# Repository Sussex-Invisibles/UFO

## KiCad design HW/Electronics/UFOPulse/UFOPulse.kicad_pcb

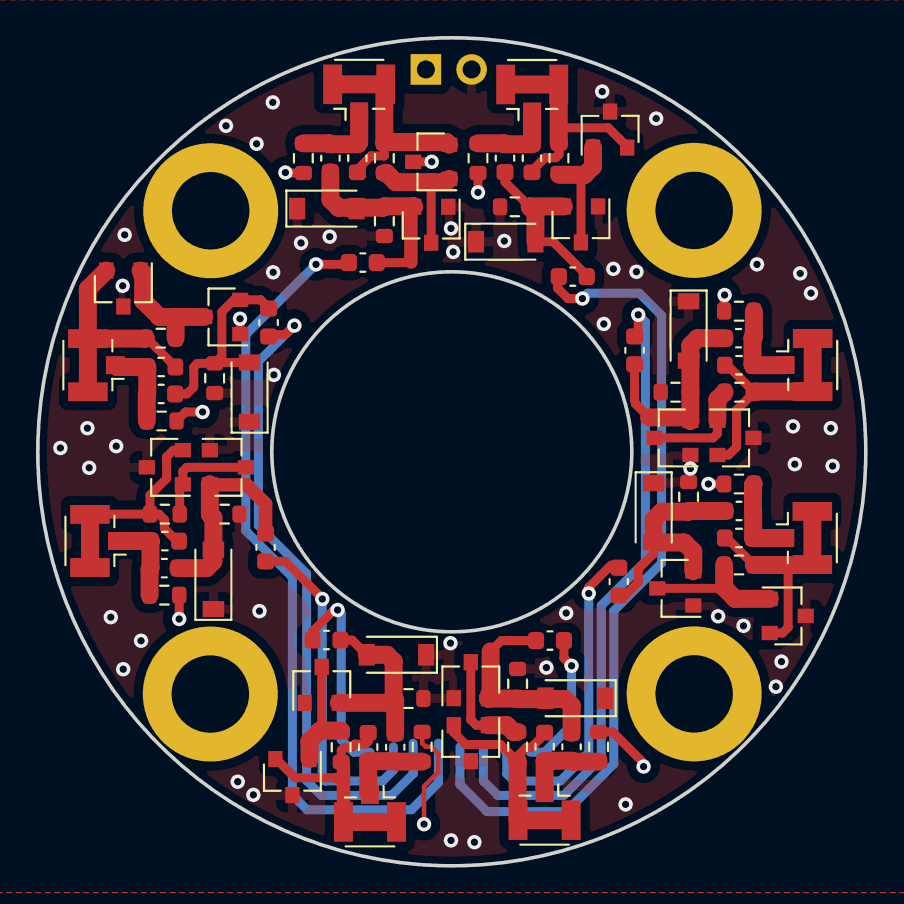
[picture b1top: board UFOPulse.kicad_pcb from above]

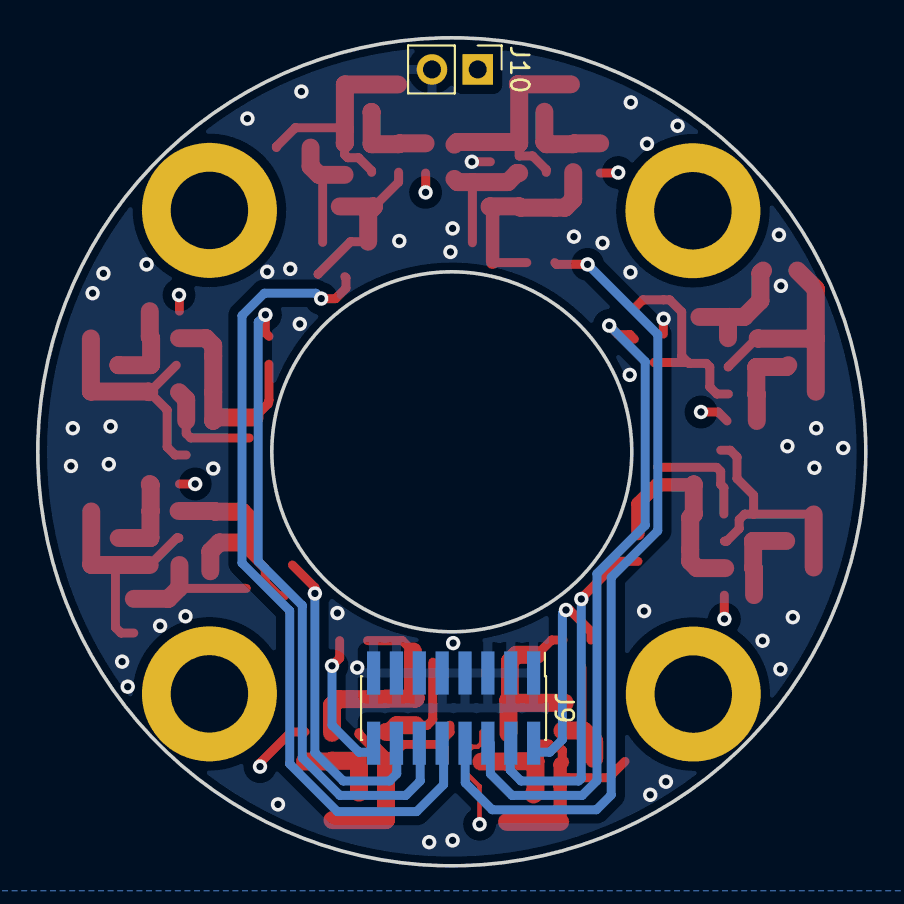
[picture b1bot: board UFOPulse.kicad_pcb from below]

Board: 4 copper layers, 46.0 x 46.0 mm, 86 parts (2 on the bottom side), 42 nets.

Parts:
C1, C3, C5, C7, C9, C11, C13, C15: 47p; C_0603_1608Metric
C2, C4, C6, C8, C10, C12, C14, C16: 1n; C_0603_1608Metric
D1, D3, D5, D7, D9, D11, D13, D15: D; D_SOD-123
H1, H2, H3, H4: MountingHole; MountingHole_4.3mm_M4_DIN965_Pad
J1, J2, J3, J4, J5, J6, J7, J8: Conn_Coaxial; U.FL_Hirose_U.FL-R-SMT-1_Vertical
J9: Conn_02x08_Odd_Even; PinHeader_2x08_P1.27mm_Vertical_SMD
J10: Conn_01x02_Female; PinHeader_1x02_P2.54mm_Vertical
L1, L2, L3, L4, L5, L6, L7, L8: 100n; L_0603_1608Metric
Q1, Q3, Q5, Q7, Q9, Q11, Q13, Q15: MMBTH10; SOT-23
Q2, Q4, Q6, Q8, Q10, Q12, Q14, Q16: MMBTH81; SOT-23
R1, R4, R7, R10, R13, R16, R19, R22: 100k; R_0603_1608Metric
R2, R5, R8, R11, R14, R17, R20, R23: 2.2k; R_0603_1608Metric
R3, R6, R9, R12, R15, R18, R21, R24: 10k; R_0603_1608Metric

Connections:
GND: D1.1 (K), D3.1 (K), D5.1 (K), D7.1 (K), D9.1 (K), D11.1 (K), D13.1 (K), D15.1 (K), J9.1, J9.3, J9.5, J9.7, J9.9, J9.11, J9.13, J9.15, J10.2, Q1.1 (B), Q2.3 (C), Q3.1 (B), Q4.3 (C), Q5.1 (B), Q6.3 (C), Q7.1 (B), Q8.3 (C), Q9.1 (B), Q10.3 (C), Q11.1 (B), Q12.3 (C), Q13.1 (B), Q14.3 (C), Q15.1 (B), Q16.3 (C), R2.2, R5.2, R8.2, R11.2, R14.2, R17.2, R20.2, R23.2
unnamed: C1.1, C2.2, D1.2 (A), Q1.2 (E), R2.1
unnamed: C2.1, J1.1 (In), L1.1, R1.1
unnamed: C3.1, C4.2, D3.2 (A), Q3.2 (E), R5.1
unnamed: C4.1, J2.1 (In), L2.1, R4.1
unnamed: C5.1, C6.2, D5.2 (A), Q5.2 (E), R8.1
unnamed: C6.1, J3.1 (In), L3.1, R7.1
unnamed: C7.1, C8.2, D7.2 (A), Q7.2 (E), R11.1
unnamed: C8.1, J4.1 (In), L4.1, R10.1
unnamed: C10.1, J5.1 (In), L5.1, R13.1
unnamed: C9.1, C10.2, D9.2 (A), Q9.2 (E), R14.1
unnamed: C11.1, C12.2, D11.2 (A), Q11.2 (E), R17.1
unnamed: C12.1, J6.1 (In), L6.1, R16.1
unnamed: C13.1, C14.2, D13.2 (A), Q13.2 (E), R20.1
unnamed: C14.1, J7.1 (In), L7.1, R19.1
unnamed: C15.1, C16.2, D15.2 (A), Q15.2 (E), R23.1
unnamed: C16.1, J8.1 (In), L8.1, R22.1
unnamed: J1.2 (Ext), L1.2, Q2.2 (E), R3.1
unnamed: J2.2 (Ext), L2.2, Q4.2 (E), R6.1
unnamed: J3.2 (Ext), L3.2, Q6.2 (E), R9.1
unnamed: J4.2 (Ext), L4.2, Q8.2 (E), R12.1
unnamed: J5.2 (Ext), L5.2, Q10.2 (E), R15.1
unnamed: J6.2 (Ext), L6.2, Q12.2 (E), R18.1
unnamed: J7.2 (Ext), L7.2, Q14.2 (E), R21.1
unnamed: J8.2 (Ext), L8.2, Q16.2 (E), R24.1
unnamed: Q1.3 (C), Q2.1 (B), R3.2
unnamed: Q3.3 (C), Q4.1 (B), R6.2
unnamed: Q5.3 (C), Q6.1 (B), R9.2
unnamed: Q7.3 (C), Q8.1 (B), R12.2
unnamed: Q9.3 (C), Q10.1 (B), R15.2
unnamed: Q11.3 (C), Q12.1 (B), R18.2
unnamed: Q13.3 (C), Q14.1 (B), R21.2
unnamed: Q15.3 (C), Q16.1 (B), R24.2
TRIG0: C9.2, J9.2
TRIG1: C1.2, J9.4
TRIG2: C11.2, J9.6
TRIG3: C3.2, J9.8
TRIG4: C13.2, J9.10
TRIG5: C5.2, J9.12
TRIG6: C15.2, J9.14
TRIG7: C7.2, J9.16
VCC: J10.1, R1.2, R4.2, R7.2, R10.2, R13.2, R16.2, R19.2, R22.2

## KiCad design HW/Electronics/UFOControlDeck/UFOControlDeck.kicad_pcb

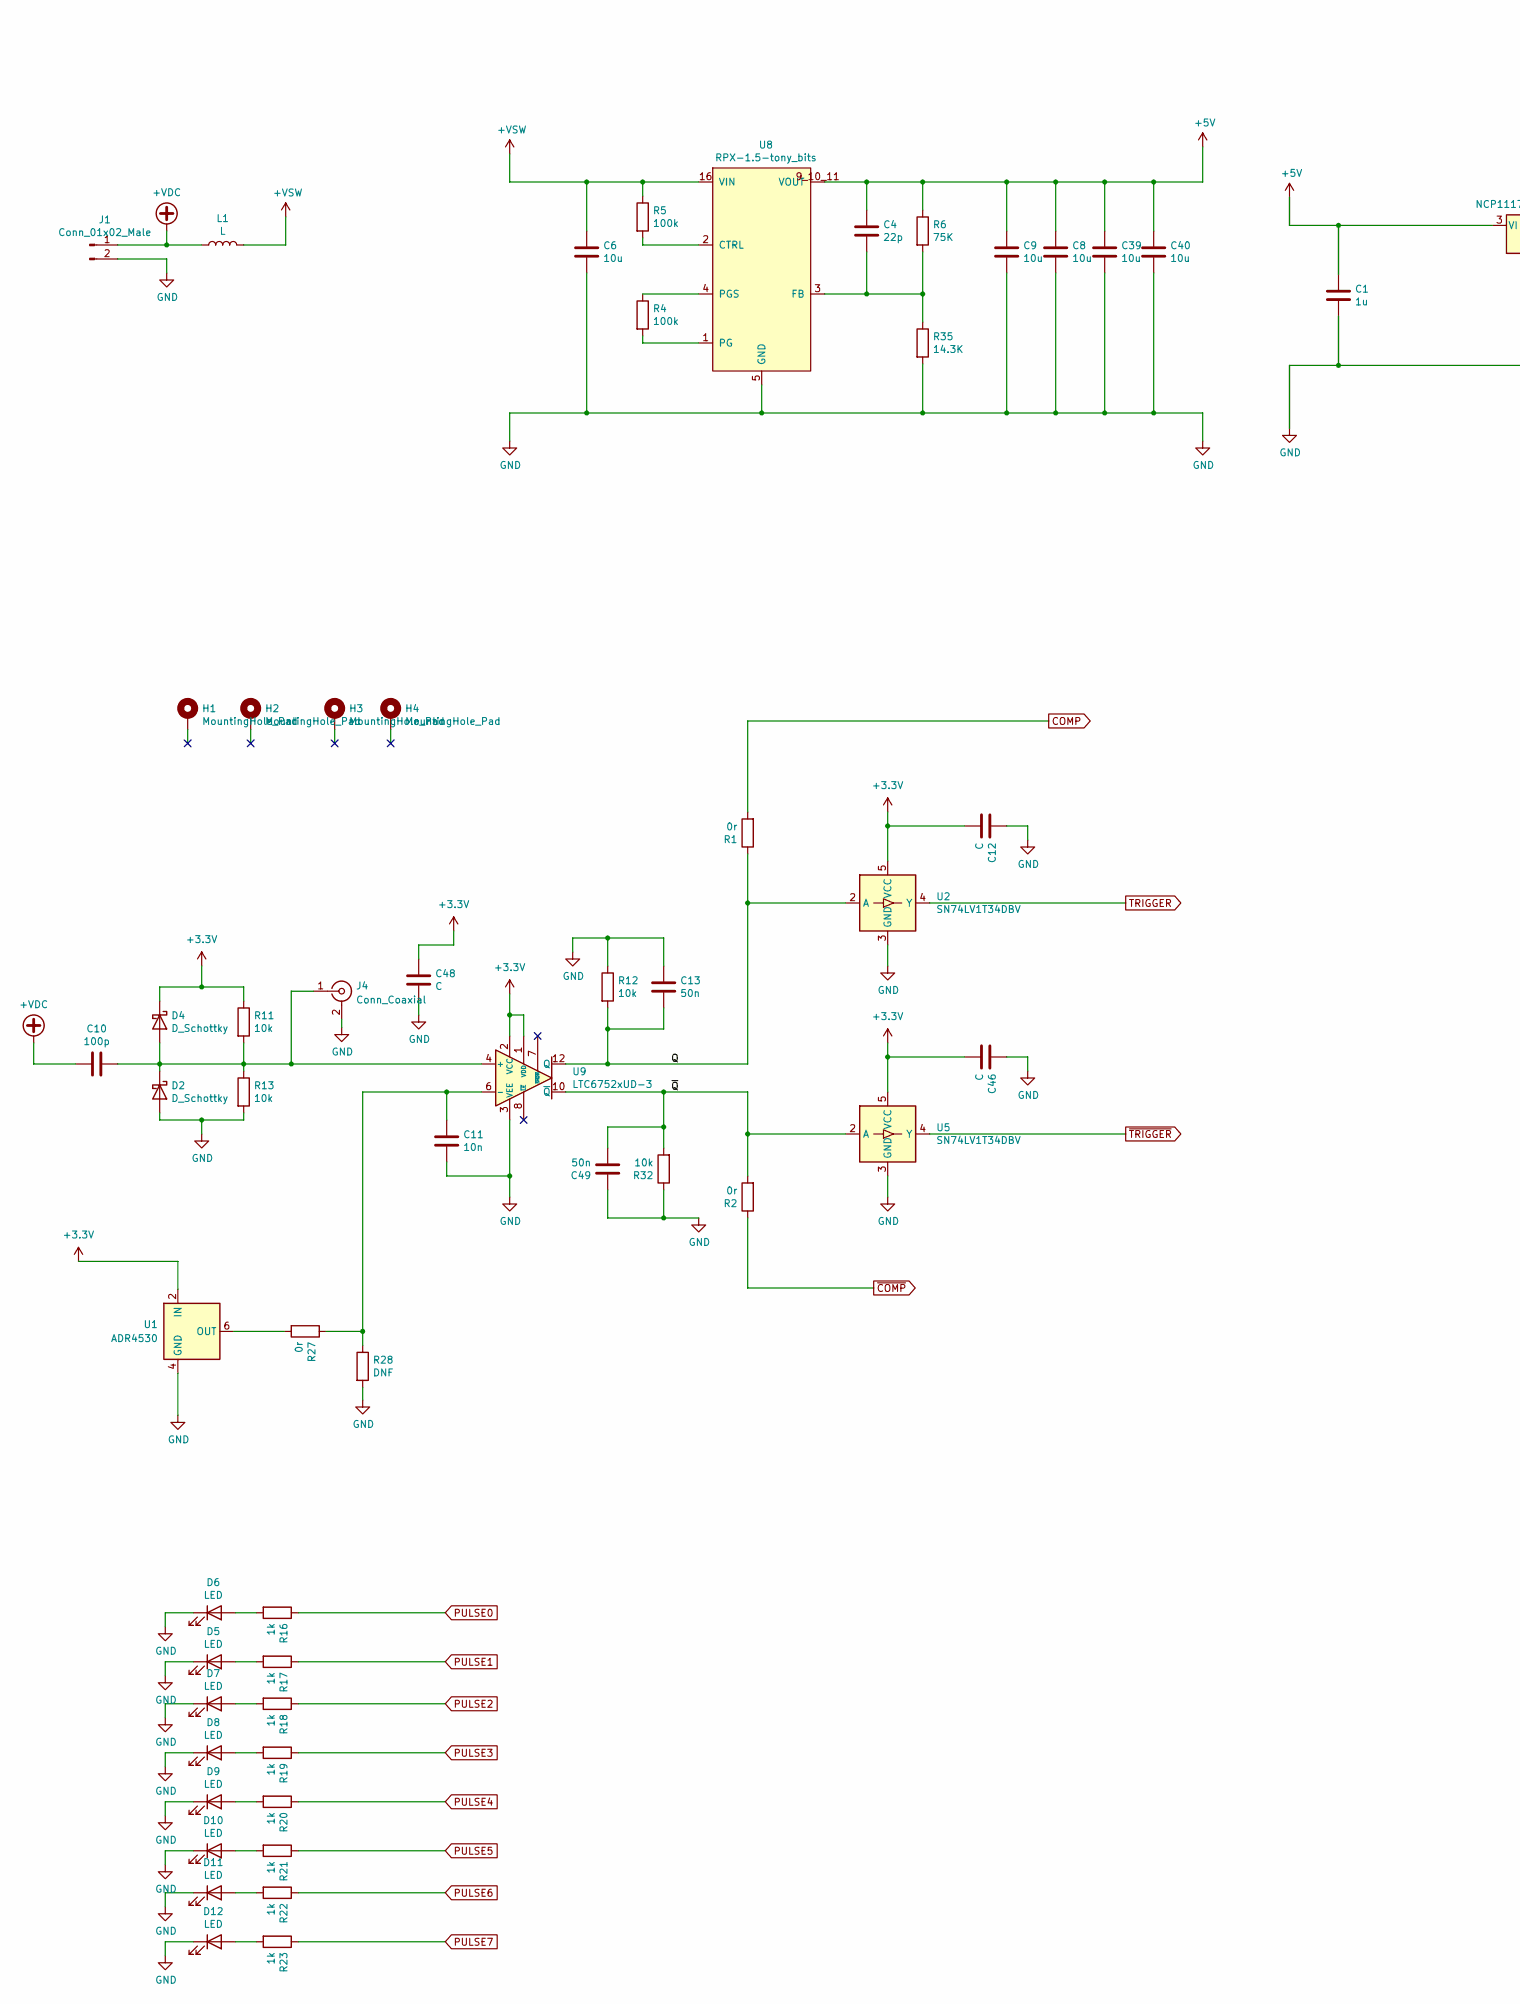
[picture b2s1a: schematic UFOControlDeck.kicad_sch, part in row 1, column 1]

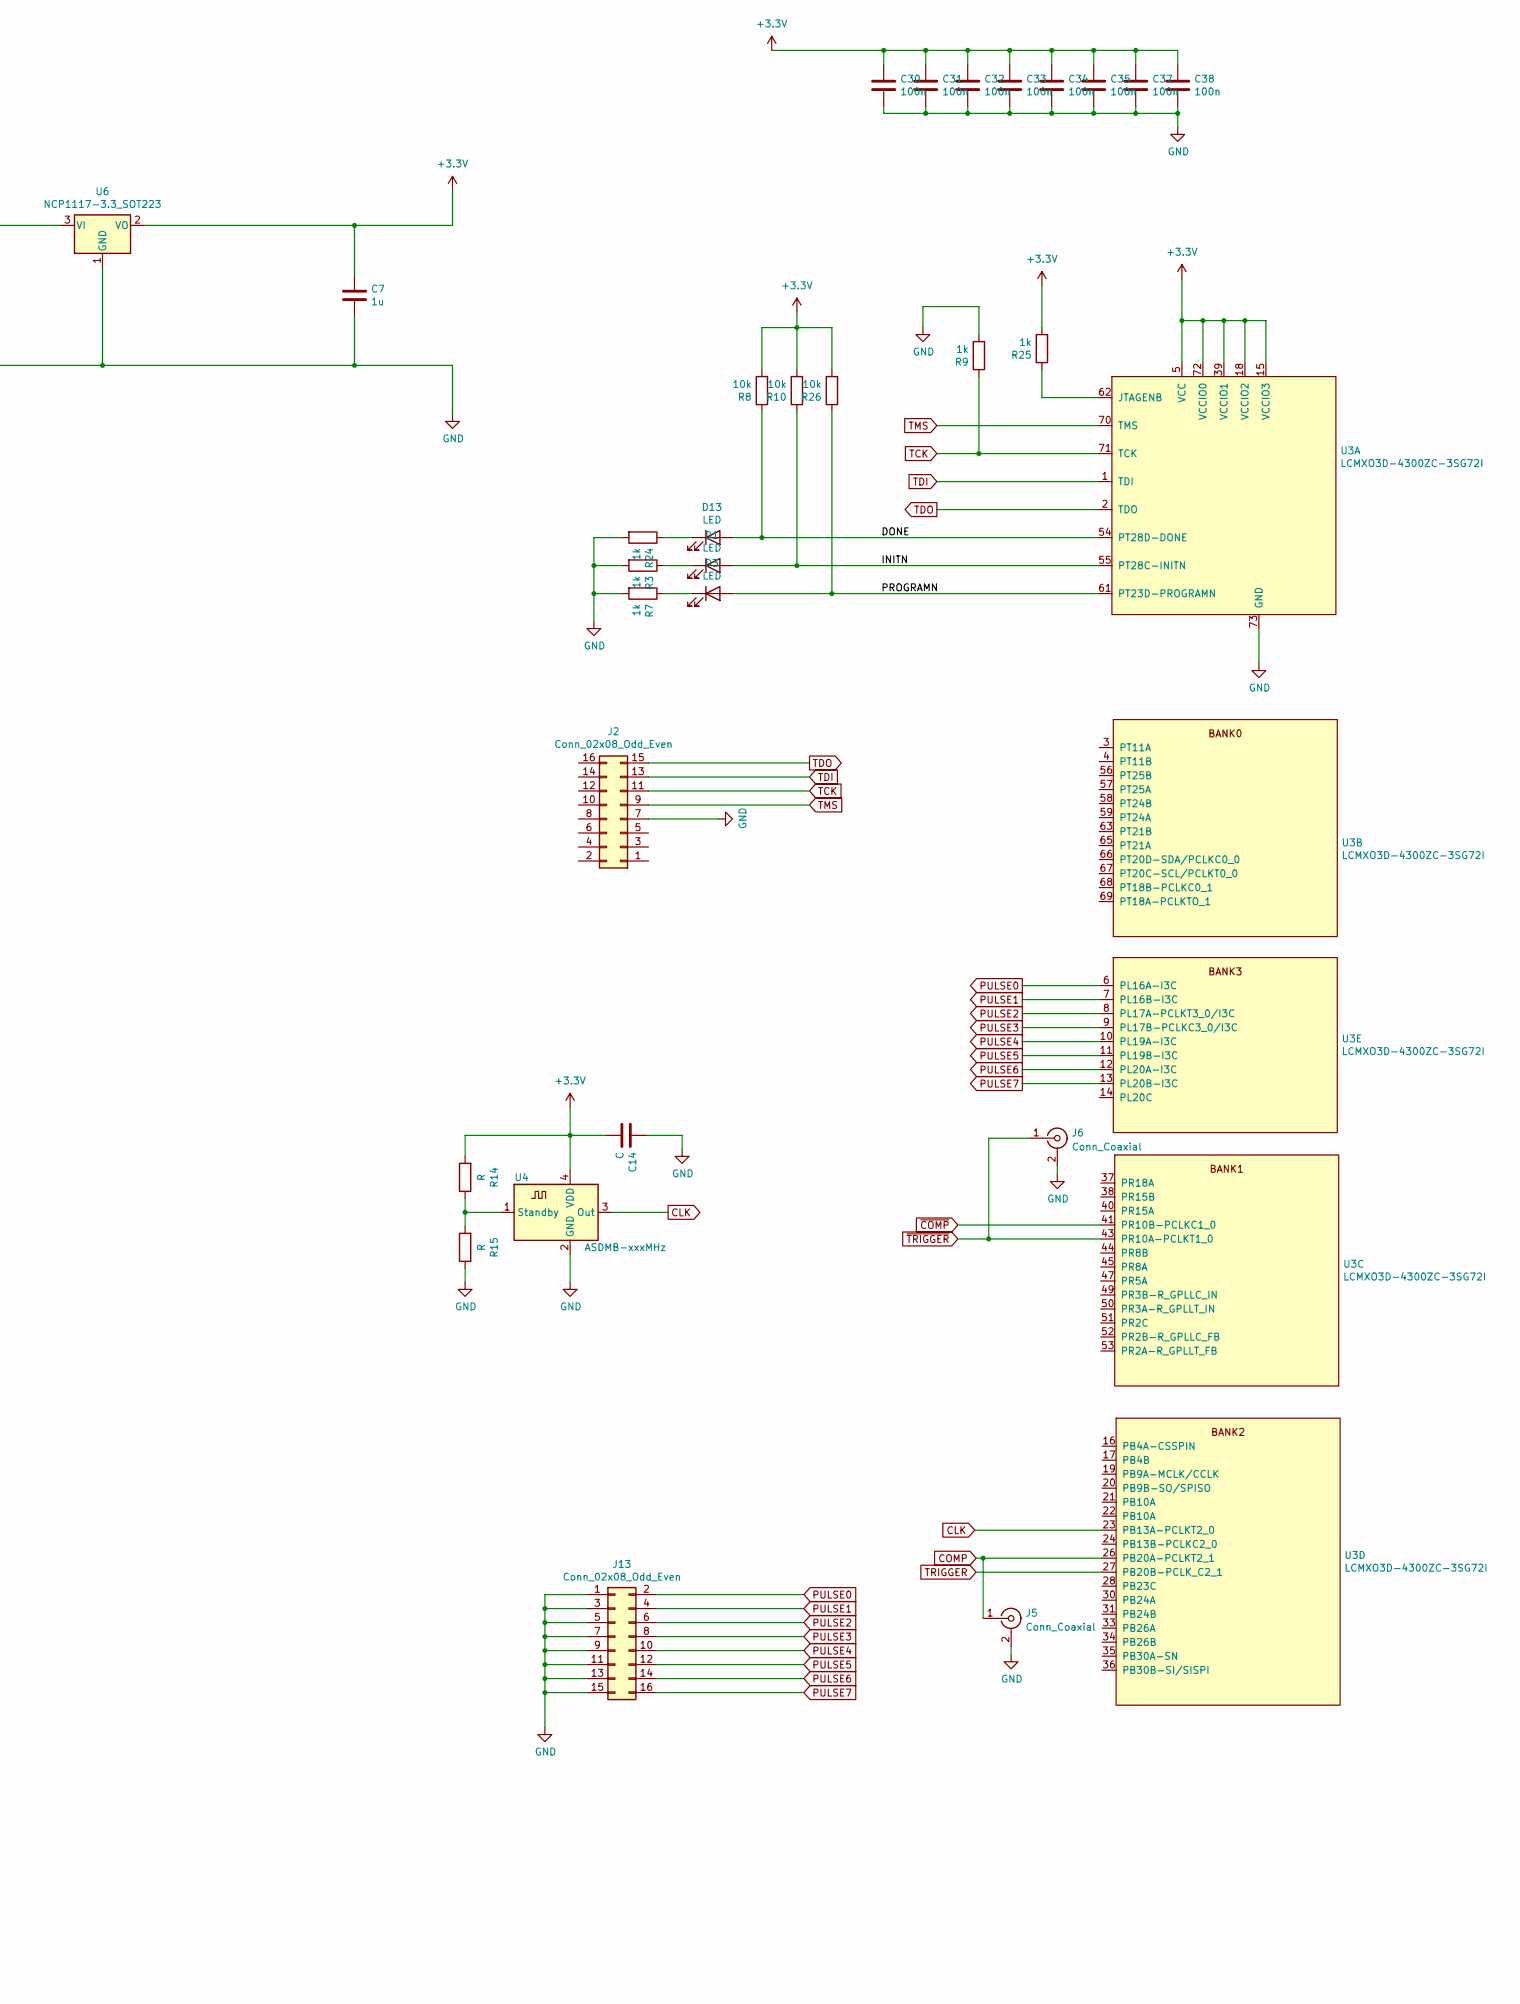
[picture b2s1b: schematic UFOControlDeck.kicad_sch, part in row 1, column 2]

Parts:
C1, C7: 1u; C_0603_1608Metric_Pad1.08x0.95mm_HandSolder
C4: 22p; C_0603_1608Metric_Pad1.08x0.95mm_HandSolder
C6, C8, C9, C39, C40: 10u; C_0603_1608Metric_Pad1.08x0.95mm_HandSolder
C10: 100p; C_0603_1608Metric_Pad1.08x0.95mm_HandSolder
C11: 10n; C_0603_1608Metric_Pad1.08x0.95mm_HandSolder
C12, C14, C46, C48: C; C_0603_1608Metric_Pad1.08x0.95mm_HandSolder
C13, C49: 50n; C_0603_1608Metric_Pad1.08x0.95mm_HandSolder
C30, C31, C32, C33, C34, C35, C37, C38: 100n; C_0603_1608Metric_Pad1.08x0.95mm_HandSolder
D1, D3, D5, D6, D7, D8, D9, D10, D11, D12, D13: LED; LED_0603_1608Metric_Pad1.05x0.95mm_HandSolder
D2, D4: D_Schottky; D_0603_1608Metric_Pad1.05x0.95mm_HandSolder
H1, H2, H3, H4: MountingHole_Pad; MountingHole_4.3mm_M4_DIN965_Pad
J1: Conn_01x02_Male; PinHeader_1x02_P2.54mm_Vertical
J2: Conn_02x08_Odd_Even; PinSocket_2x08_P1.27mm_Vertical_SMD
J4, J5, J6: Conn_Coaxial; U.FL_Hirose_U.FL-R-SMT-1_Vertical
J13: Conn_02x08_Odd_Even; PinHeader_2x08_P1.27mm_Vertical_SMD
L1: L; L_Taiyo-Yuden_NR-40xx
R1, R2, R27: 0r; R_0603_1608Metric_Pad0.98x0.95mm_HandSolder
R3, R7, R9, R16, R17, R18, R19, R20, R21, R22, R23, R24, R25: 1k; R_0603_1608Metric_Pad0.98x0.95mm_HandSolder
R4, R5: 100k; R_0603_1608Metric_Pad0.98x0.95mm_HandSolder
R6: 75K; R_0603_1608Metric_Pad0.98x0.95mm_HandSolder
R8, R10, R11, R12, R13, R26, R32: 10k; R_0603_1608Metric_Pad0.98x0.95mm_HandSolder
R14, R15: R; R_0603_1608Metric_Pad0.98x0.95mm_HandSolder
R28: DNF; R_0603_1608Metric_Pad0.98x0.95mm_HandSolder
R35: 14.3K; R_0603_1608Metric_Pad0.98x0.95mm_HandSolder
U1: ADR4530; SOIC-8_3.9x4.9mm_P1.27mm
U2, U5: SN74LV1T34DBV; SOT-23-5
U3: LCMXO3D-4300ZC-3SG72I; QFN-72-1EP_10x10mm_P0.5mm_EP6x6mm_ThermalVias
U4: ASDMB-xxxMHz; Oscillator_SMD_Abracon_ASDMB-4Pin_2.5x2.0mm
U6: NCP1117-3.3_SOT223; SOT-223-3_TabPin2
U8: RPX-1.5-tony_bits; CONV_RPX-1.5-R
U9: LTC6752xUD-3; QFN-12-1EP_3x3mm_P0.5mm_EP1.65x1.65mm

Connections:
+3.3V: C7.1, C12.2, C14.2, C30.1, C31.1, C32.1, C33.1, C34.1, C35.1, C37.1, C38.1, C46.2, C48.1, D4.1 (K), R8.2, R10.2, R11.1, R14.2, R25.2, R26.2, U1.2 (IN), U2.5 (VCC), U3.5 (VCC), U3.15 (VCCIO3), U3.18 (VCCIO2), U3.25 (VCCIO2), U3.29 (VCC), U3.32 (VCCIO2), U3.39 (VCCIO1), U3.42 (VCCIO1), U3.46 (VCC), U3.48 (VCCIO1), U3.60 (VCCIO0), U3.64 (VCCIO0), U3.72 (VCCIO0), U4.4 (VDD), U5.5 (VCC), U6.2 (VO), U9.1 (VDD), U9.2 (VCC)
+5V: C1.1, C4.1, C8.1, C9.1, C39.1, C40.1, R6.1, U6.3 (VI), U8.9_10_11 (VOUT)
+VDC: C10.2, J1.1, L1.1
+VSW: C6.1, L1.2, R5.1, U8.16 (VIN)
/DONE: D13.2 (A), R8.1, U3.54 (PT28D-DONE)
/INITN: D1.2 (A), R10.1, U3.55 (PT28C-INITN)
/PROGRAMN: D3.2 (A), R26.1, U3.61 (PT23D-PROGRAMN)
/Q: C13.2, R1.1, R12.2, U2.2 (A), U9.12 (Q)
/~Q: C49.2, R2.2, R32.2, U5.2 (A), U9.10 (~Q)
CLK: U3.23 (PB13A-PCLKT2_0), U4.3 (Out)
COMP: J5.1 (In), R1.2, U3.26 (PB20A-PCLKT2_1)
GND: C1.2, C6.2, C7.2, C8.2, C9.2, C11.2, C12.1, C13.1, C14.1, C30.2, C31.2, C32.2, C33.2, C34.2, C35.2, C37.2, C38.2, C39.2, C40.2, C46.1, C48.2, C49.1, D2.2 (A), D5.1 (K), D6.1 (K), D7.1 (K), D8.1 (K), D9.1 (K), D10.1 (K), D11.1 (K), D12.1 (K), J1.2, J2.7, J4.2 (Ext), J5.2 (Ext), J6.2 (Ext), J13.1, J13.3, J13.5, J13.7, J13.9, J13.11, J13.13, J13.15, R3.2, R7.2, R9.2, R12.1, R13.2, R15.1, R24.2, R28.2, R32.1, R35.2, U1.4 (GND), U2.3 (GND), U3.73 (GND), U4.2 (GND), U5.3 (GND), U6.1 (GND), U8.5 (GND), U8.14 (GND), U8.15 (GND), U9.3 (VEE), U9.9 (VEE), U9.13 (VEE)
unnamed: C4.2, R6.2, R35.1, U8.3 (FB)
unnamed: C10.1, D2.1 (K), D4.2 (A), J4.1 (In), R11.2, R13.1, U9.4 (+)
unnamed: C11.1, R27.1, R28.1, U9.6 (-)
unnamed: D1.1 (K), R3.1
unnamed: D3.1 (K), R7.1
unnamed: D5.2 (A), R17.2
unnamed: D6.2 (A), R16.2
unnamed: D7.2 (A), R18.2
unnamed: D8.2 (A), R19.2
unnamed: D9.2 (A), R20.2
unnamed: D10.2 (A), R21.2
unnamed: D11.2 (A), R22.2
unnamed: D12.2 (A), R23.2
unnamed: D13.1 (K), R24.1
unnamed: R4.1, U8.4 (PGS)
unnamed: R4.2, U8.1 (PG)
unnamed: R5.2, U8.2 (CTRL)
unnamed: R14.1, R15.2, U4.1 (Standby)
unnamed: R25.1, U3.62 (JTAGENB)
unnamed: R27.2, U1.6 (OUT)
PULSE0: J13.2, R16.1, U3.6 (PL16A-I3C)
PULSE1: J13.4, R17.1, U3.7 (PL16B-I3C)
PULSE2: J13.6, R18.1, U3.8 (PL17A-PCLKT3_0/I3C)
PULSE3: J13.8, R19.1, U3.9 (PL17B-PCLKC3_0/I3C)
PULSE4: J13.10, R20.1, U3.10 (PL19A-I3C)
PULSE5: J13.12, R21.1, U3.11 (PL19B-I3C)
PULSE6: J13.14, R22.1, U3.12 (PL20A-I3C)
PULSE7: J13.16, R23.1, U3.13 (PL20B-I3C)
TCK: J2.11, R9.1, U3.71 (TCK)
TDI: J2.13, U3.1 (TDI)
TDO: J2.15, U3.2 (TDO)
TMS: J2.9, U3.70 (TMS)
TRIGGER: U2.4 (Y), U3.27 (PB20B-PCLK_C2_1)
~COMP: R2.1, U3.41 (PR10B-PCLKC1_0)
~TRIGGER: J6.1 (In), U3.43 (PR10A-PCLKT1_0), U5.4 (Y)

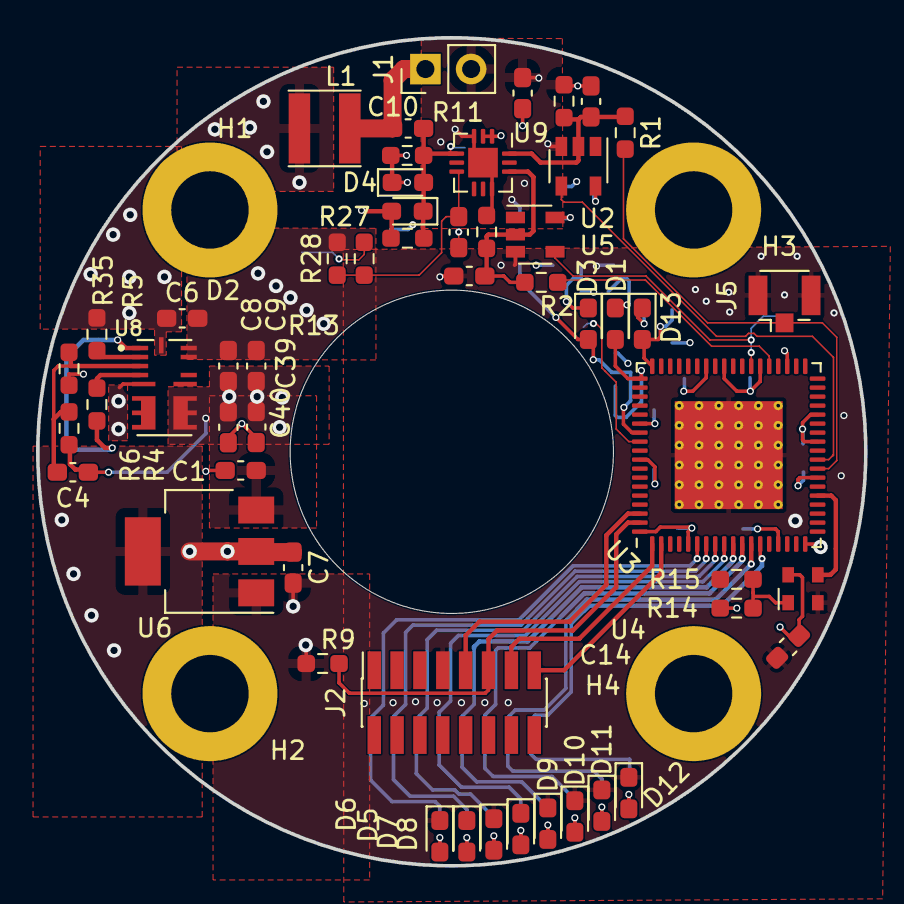
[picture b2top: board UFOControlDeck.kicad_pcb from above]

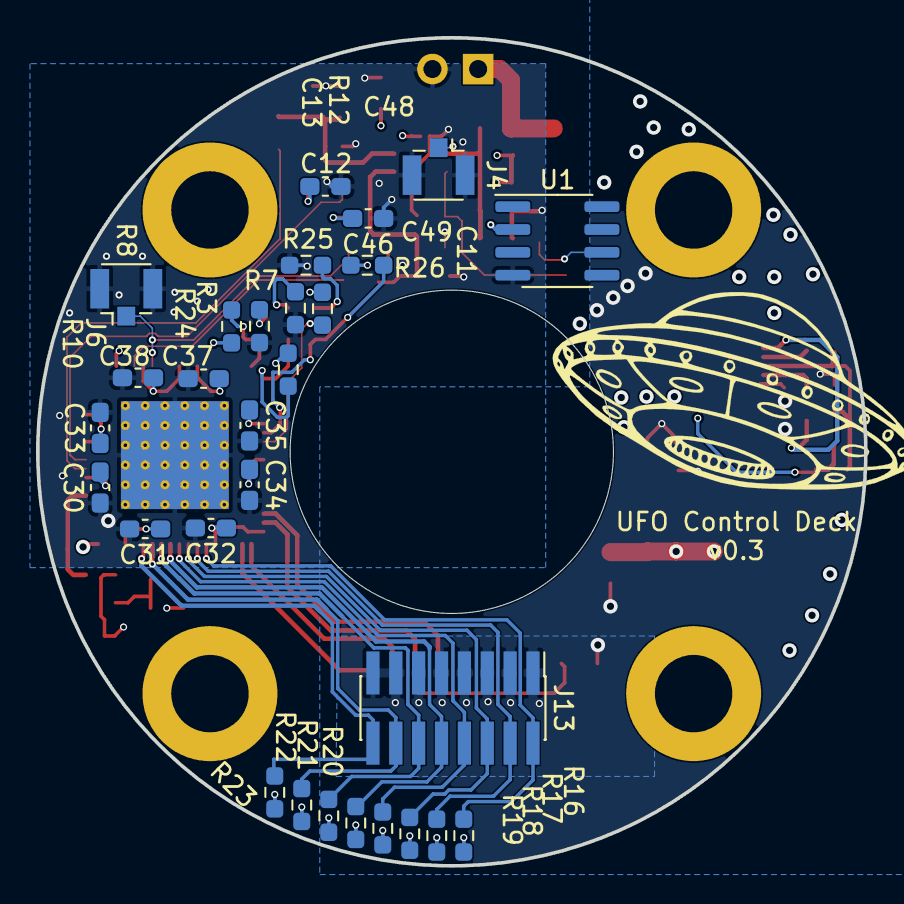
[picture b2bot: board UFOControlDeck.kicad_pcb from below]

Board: 4 copper layers, 46.0 x 46.0 mm, 86 parts (29 on the bottom side), 47 nets.

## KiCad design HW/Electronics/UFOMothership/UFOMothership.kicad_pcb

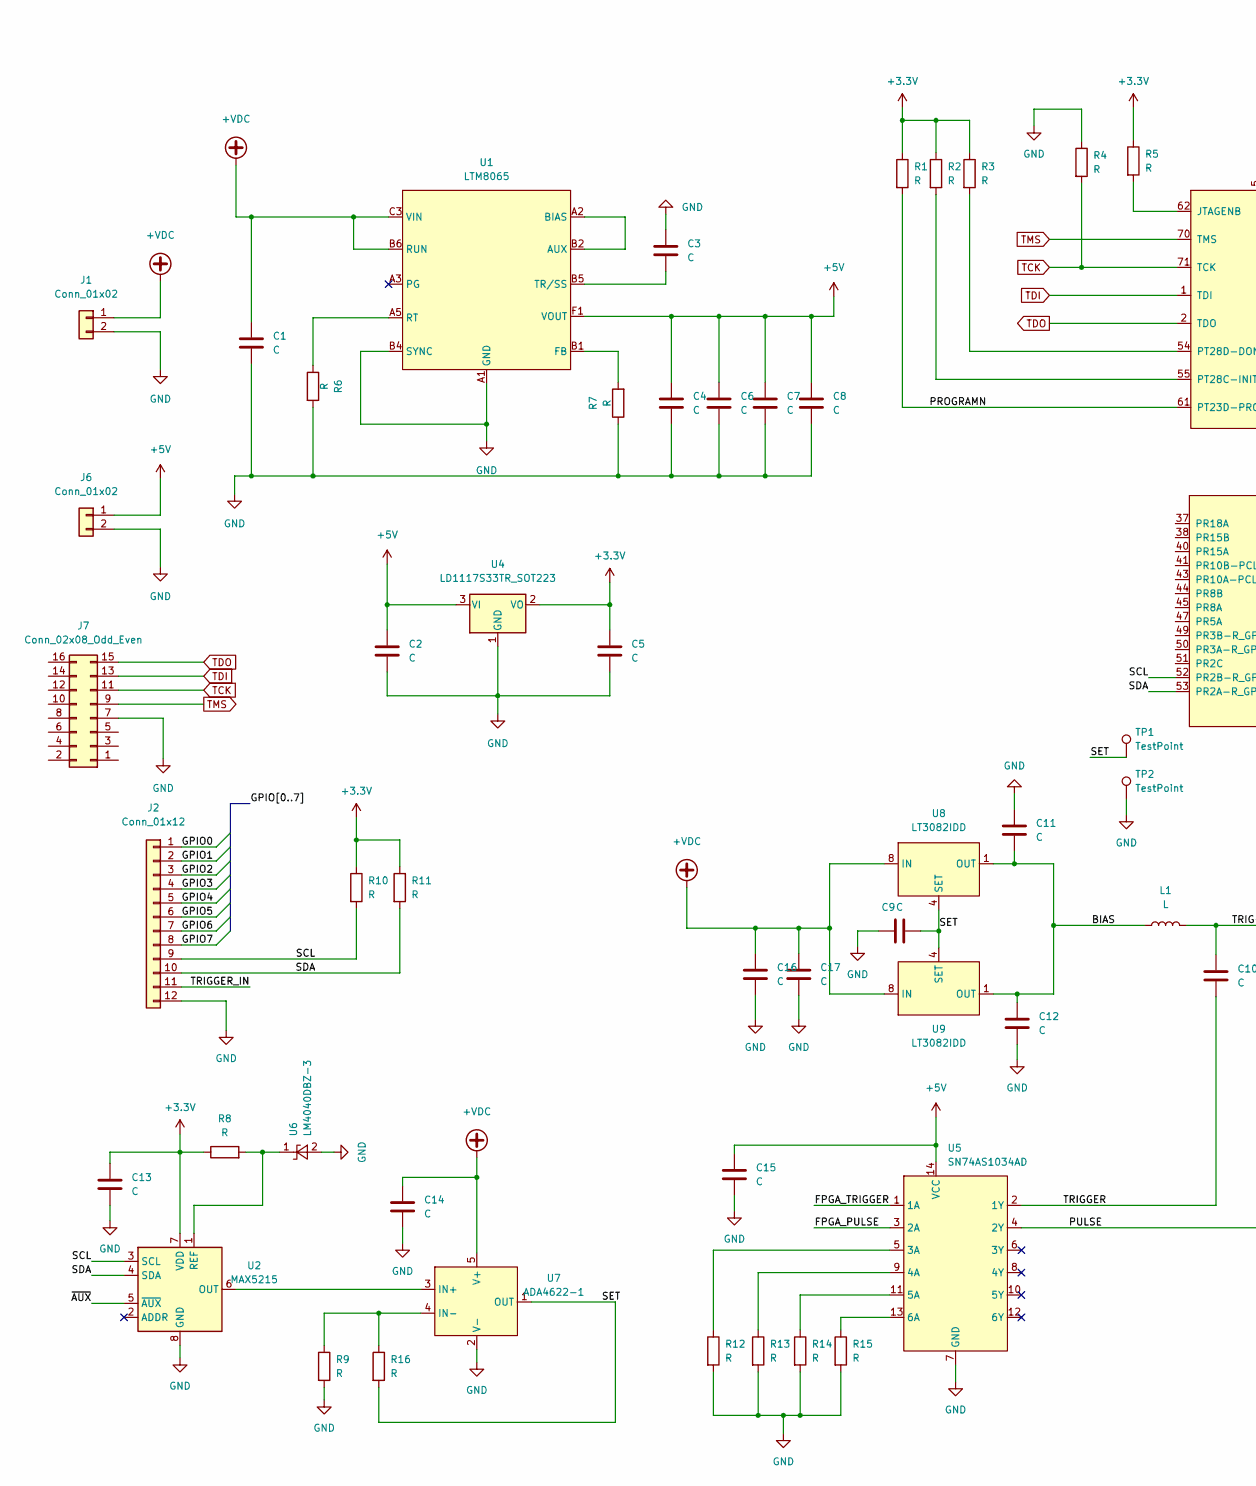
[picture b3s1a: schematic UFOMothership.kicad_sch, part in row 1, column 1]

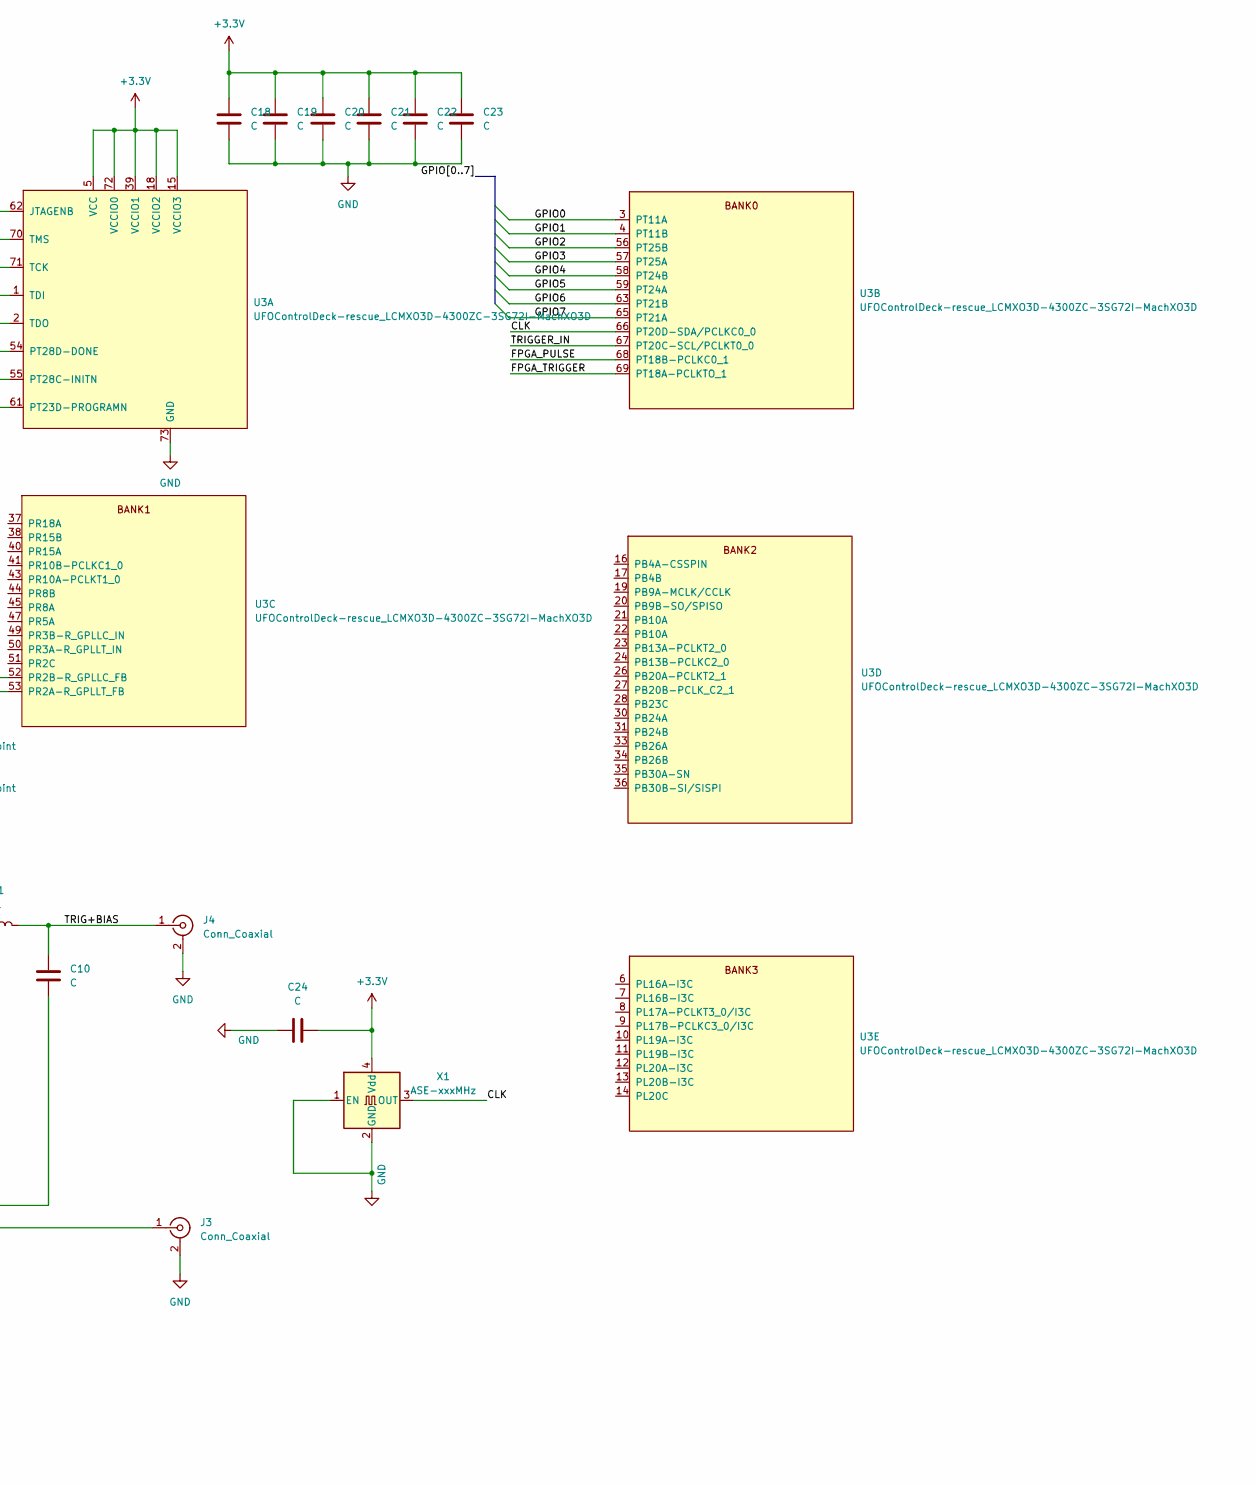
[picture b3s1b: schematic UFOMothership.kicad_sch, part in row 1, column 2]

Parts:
C1, C2, C3, C4, C5, C6, C7, C8, C9, C10, C11, C12, C13, C14, C15, C16, C17, C18, C19, C20, C21, C22, C23, C24: C; C_0603_1608Metric_Pad1.08x0.95mm_HandSolder
J1, J6: Conn_01x02; PinHeader_1x02_P2.54mm_Vertical
J2: Conn_01x12; PinHeader_1x12_P2.54mm_Vertical
J3, J4: Conn_Coaxial; SMA_Molex_73251-2120_EdgeMount_Horizontal
J7: Conn_02x08_Odd_Even; PinSocket_2x08_P1.27mm_Vertical_SMD
L1: L; L_Taiyo-Yuden_NR-40xx_HandSoldering
R1, R2, R3, R4, R5, R6, R7, R8, R9, R10, R11, R12, R13, R14, R15, R16: R; R_0603_1608Metric_Pad0.98x0.95mm_HandSolder
TP1, TP2: TestPoint; TestPoint_Keystone_5015_Micro-Minature
U1: LTM8065; BGA-36_6x6_6.25x6.25mm
U2: MAX5215; MSOP-8_3x3mm_P0.65mm
U3: UFOControlDeck-rescue_LCMXO3D-4300ZC-3SG72I-MachX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; QFN-72-1EP_10x10mm_P0.5mm_EP6x6mm_ThermalVias
U4: LD1117S33TR_SOT223; SOT-223-3_TabPin2
U5: SN74AS1034AD; SOIC-14_3.9x8.7mm_P1.27mm
U6: LM4040DBZ-3; SOT-23
U7: ADA4622-1; SOT-23-5
U8, U9: LT3082IDD; DFN-8-1EP_3x3mm_P0.5mm_EP1.65x2.38mm_ThermalVias
X1: ASE-xxxMHz; Oscillator_SMD_Abracon_ASE-4Pin_3.2x2.5mm

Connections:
+3.3V: C5.1, C13.1, C18.1, C19.1, C20.1, C21.1, C22.1, C23.1, C24.2, R1.1, R2.1, R3.1, R5.1, R8.1, R10.1, R11.1, U2.7 (VDD), U3.5 (VCC), U3.15 (VCCIO3), U3.18 (VCCIO2), U3.25 (VCCIO2), U3.29 (VCC), U3.32 (VCCIO2), U3.39 (VCCIO1), U3.42 (VCCIO1), U3.46 (VCC), U3.48 (VCCIO1), U3.60 (VCCIO0), U3.64 (VCCIO0), U3.72 (VCCIO0), U4.2 (VO), X1.4 (Vdd)
+5V: C2.1, C4.1, C6.1, C7.1, C8.1, C15.1, J6.1, U1.F1 (VOUT), U1.F2 (VOUT), U1.F3 (VOUT), U1.F4 (VOUT), U1.F5 (VOUT), U1.F6 (VOUT), U4.3 (VI), U5.14 (VCC)
+VDC: C1.1, C14.1, C16.1, C17.1, J1.1, U1.B6 (RUN), U1.C3 (VIN), U1.C4 (VIN), U1.C5 (VIN), U1.C6 (VIN), U7.5 (V+), U8.7 (IN), U8.8 (IN), U9.7 (IN), U9.8 (IN)
/BIAS: C11.2, C12.1, L1.1, U8.1 (OUT), U8.2 (OUT), U8.9 (OUT), U9.1 (OUT), U9.2 (OUT), U9.9 (OUT)
/CLK: U3.66 (PT20D-SDA/PCLKC0_0), X1.3 (OUT)
/FPGA_PULSE: U3.68 (PT18B-PCLKC0_1), U5.3 (2A)
/FPGA_TRIGGER: U3.69 (PT18A-PCLKTO_1), U5.1 (1A)
/GPIO0: J2.1, U3.3 (PT11A)
/GPIO1: J2.2, U3.4 (PT11B)
/GPIO2: J2.3, U3.56 (PT25B)
/GPIO3: J2.4, U3.57 (PT25A)
/GPIO4: J2.5, U3.58 (PT24B)
/GPIO5: J2.6, U3.59 (PT24A)
/GPIO6: J2.7, U3.63 (PT21B)
/GPIO7: J2.8, U3.65 (PT21A)
/PROGRAMN: R1.2, U3.61 (PT23D-PROGRAMN)
/PULSE: J3.1 (In), U5.4 (2Y)
/SCL: J2.9, R10.2, U2.3 (SCL), U3.52 (PR2B-R_GPLLC_FB)
/SDA: J2.10, R11.2, U2.4 (SDA), U3.53 (PR2A-R_GPLLT_FB)
/SET: C9.2, R16.2, TP1.1, U7.1 (OUT), U8.4 (SET), U9.4 (SET)
/TRIG+BIAS: C10.1, J4.1 (In), L1.2
/TRIGGER: C10.2, U5.2 (1Y)
/TRIGGER_IN: J2.11, U3.67 (PT20C-SCL/PCLKT0_0)
/~AUX: U2.5 (~AUX)
GND: C1.2, C2.2, C3.1, C4.2, C5.2, C6.2, C7.2, C8.2, C9.1, C11.1, C12.2, C13.2, C14.2, C15.2, C16.2, C17.2, C18.2, C19.2, C20.2, C21.2, C22.2, C23.2, C24.1, J1.2, J2.12, J3.2 (Ext), J4.2 (Ext), J6.2, J7.7, R4.1, R6.2, R7.1, R9.2, R12.2, R13.2, R14.2, R15.2, TP2.1, U1.A1 (GND), U1.A4 (GND), U1.A6 (GND), U1.B3 (GND), U1.B4 (SYNC), U1.C1 (GND), U1.C2 (GND), U1.D1 (GND), U1.D2 (GND), U1.D3 (GND), U1.D4 (GND), U1.D5 (GND), U1.D6 (GND), U1.E1 (GND), U1.E2 (GND), U1.E3 (GND), U1.E4 (GND), U1.E5 (GND), U1.E6 (GND), U2.8 (GND), U3.73 (GND), U4.1 (GND), U5.7 (GND), U6.2 (A), U7.2 (V-), X1.1 (EN), X1.2 (GND)
unnamed: C3.2, U1.B5 (TR/SS)
unnamed: R2.2, U3.55 (PT28C-INITN)
unnamed: R3.2, U3.54 (PT28D-DONE)
unnamed: R5.2, U3.62 (JTAGENB)
unnamed: R6.1, U1.A5 (RT)
unnamed: R7.2, U1.B1 (FB)
unnamed: R8.2, U2.1 (REF), U6.1 (K)
unnamed: R12.1, U5.5 (3A)
unnamed: R13.1, U5.9 (4A)
unnamed: R14.1, U5.11 (5A)
unnamed: R15.1, U5.13 (6A)
unnamed: R9.1, R16.1, U7.4 (IN-)
unnamed: U1.A2 (BIAS), U1.B2 (AUX)
unnamed: U2.6 (OUT), U7.3 (IN+)
TCK: J7.11, R4.2, U3.71 (TCK)
TDI: J7.13, U3.1 (TDI)
TDO: J7.15, U3.2 (TDO)
TMS: J7.9, U3.70 (TMS)

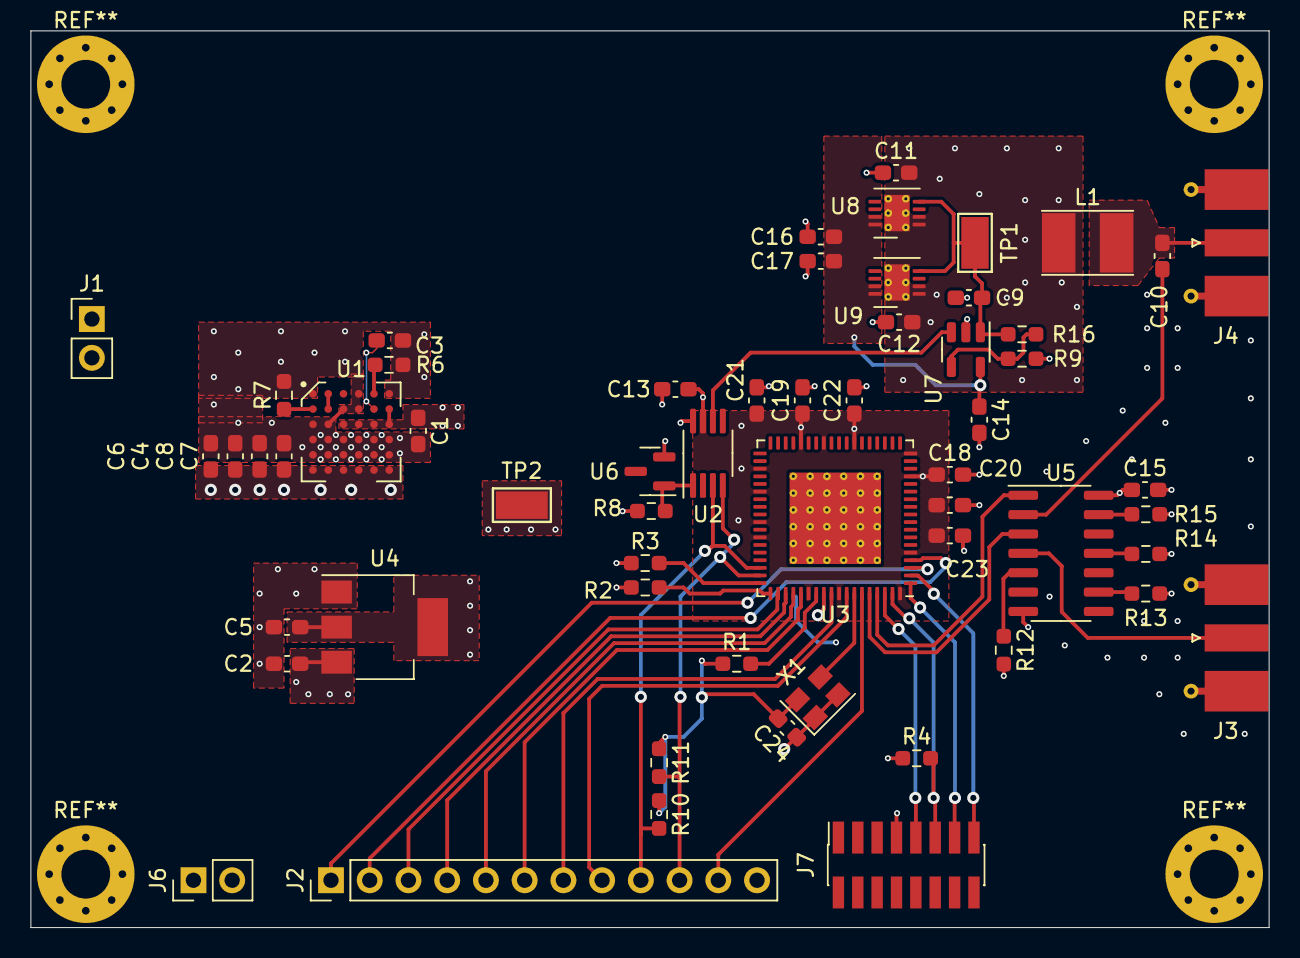
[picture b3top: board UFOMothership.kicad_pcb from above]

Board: 4 copper layers, 81.2 x 58.8 mm, 59 parts (1 on the bottom side), 42 nets.

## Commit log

2020-12-04 Archived electronics documents
2021-01-08 Added UFO specification document to Docs
2021-02-25 Added initial UFO electronic designs
2021-03-24 Added control deck Interactive BoM
2021-03-24 Updated flash in BoM
2021-04-16 Created firmware area
2021-04-16 fw blink test added
2021-04-19 modified test project
2021-07-29 added mothership design project
2021-10-22 Starting FPGA part switch to LCMXO3D-4300ZC-3SG72I
2021-10-24 pcb and schematic changes for machxo3d
2021-11-08 main changes made to swap fpga, comparator and power supplies
2021-11-11 v0.2 design manufactured but requires fixing drill size and traces as not supported by manufacturer
2022-10-28 files for manufactured mothership pulsedeck and controldeck
